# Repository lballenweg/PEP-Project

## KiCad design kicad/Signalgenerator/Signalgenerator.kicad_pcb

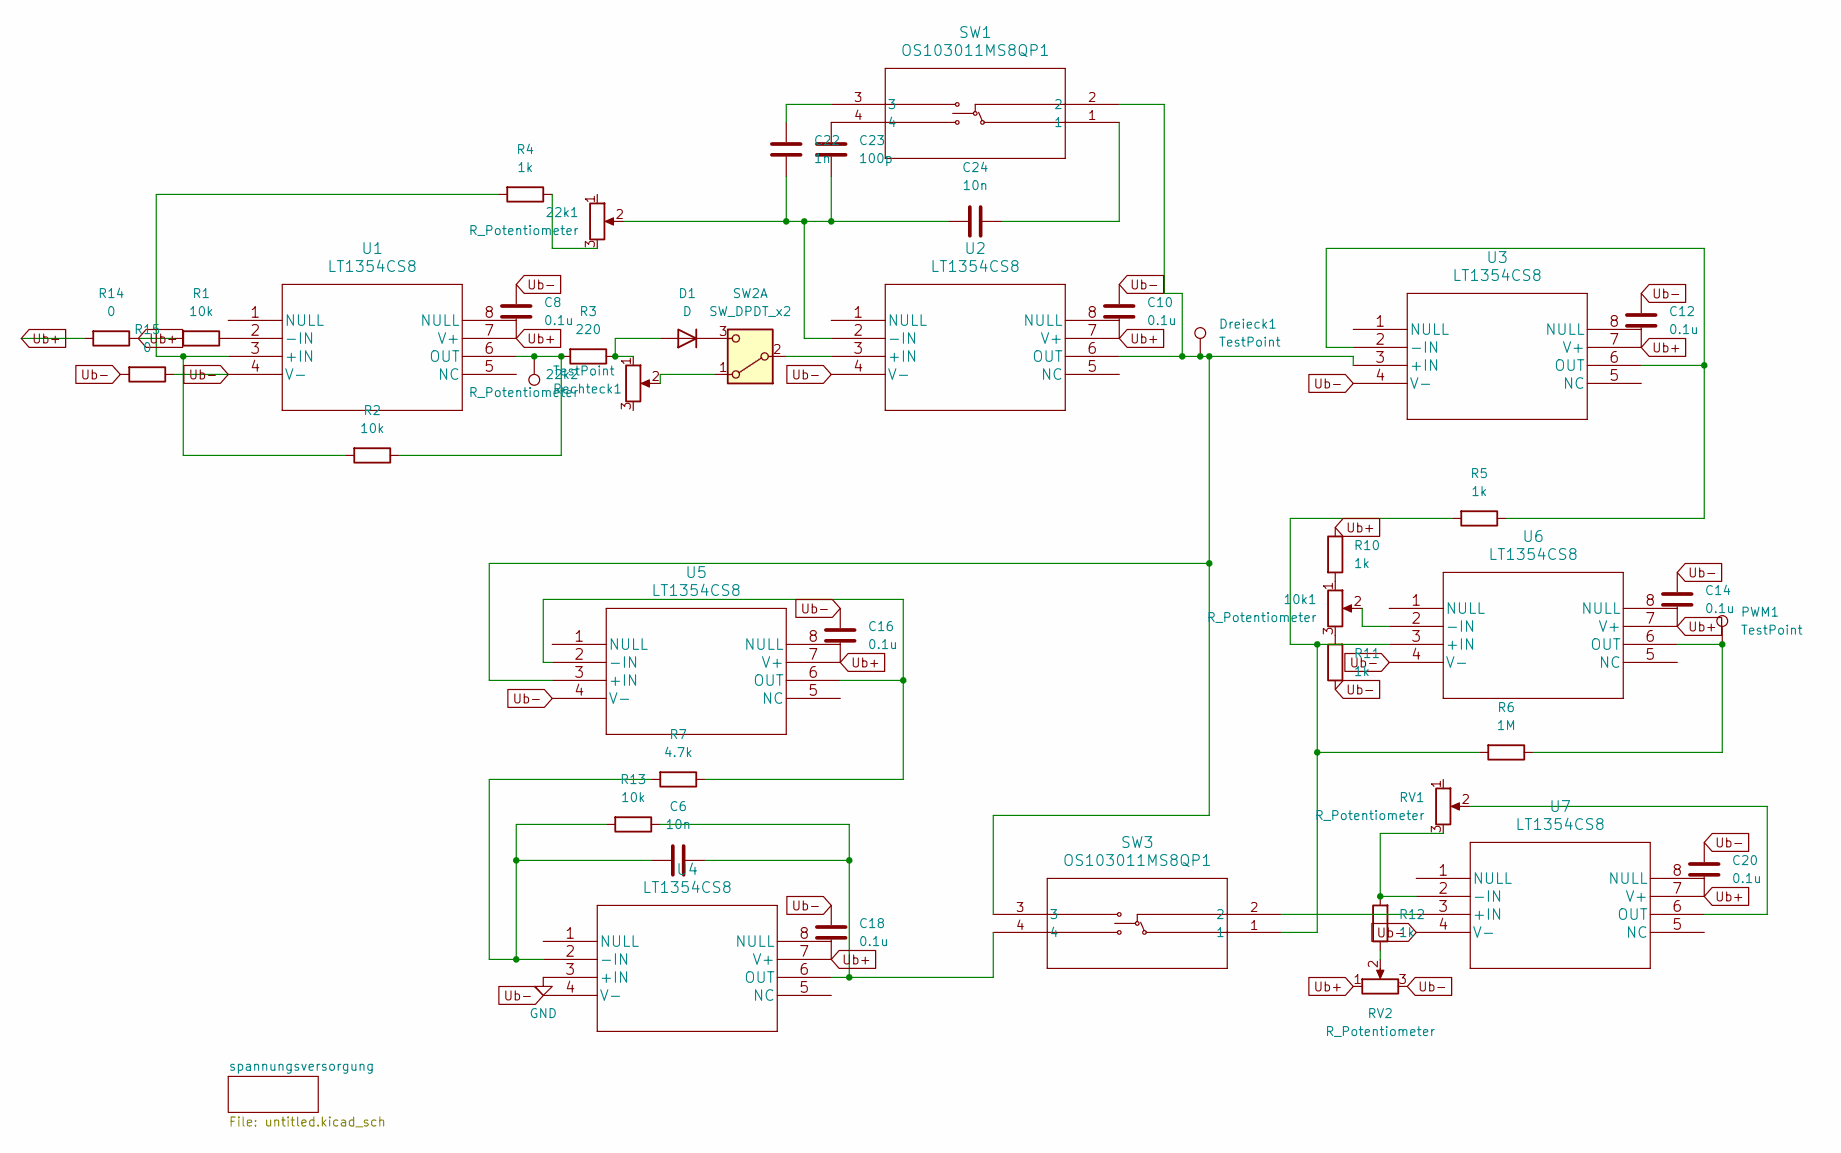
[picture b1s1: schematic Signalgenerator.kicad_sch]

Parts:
10k1, 22k1, 22k2: R_Potentiometer; Potentiometer_Vishay_T7-YA_Single_Vertical
C6, C24: 10n; C_0603_1608Metric_Pad1.08x0.95mm_HandSolder
C8, C10, C12, C14, C16, C18, C20: 0.1u; C_0603_1608Metric_Pad1.08x0.95mm_HandSolder
C22: 1n; C_0603_1608Metric_Pad1.08x0.95mm_HandSolder
C23: 100p; C_0603_1608Metric_Pad1.08x0.95mm_HandSolder
D1: D; D_A-405_P2.54mm_Vertical_AnodeUp
Dreieck1: TestPoint; TestPoint_Pad_D1.0mm
PWM1: TestPoint; TestPoint_Pad_D1.0mm
R1, R2, R13: 10k; R_0805_2012Metric_Pad1.20x1.40mm_HandSolder
R3: 220; R_0805_2012Metric_Pad1.20x1.40mm_HandSolder
R4, R5, R10, R11, R12: 1k; R_0805_2012Metric_Pad1.20x1.40mm_HandSolder
R6: 1M; R_0805_2012Metric_Pad1.20x1.40mm_HandSolder
R7: 4.7k; R_0805_2012Metric_Pad1.20x1.40mm_HandSolder
R14, R15: 0; R_0805_2012Metric_Pad1.20x1.40mm_HandSolder
RV1, RV2: R_Potentiometer; Potentiometer_Vishay_T7-YA_Single_Vertical
Rechteck1: TestPoint; TestPoint_Pad_D1.0mm
SW1, SW3: OS103011MS8QP1
SW2: SW_DPDT_x2; SW_Slide_SPDT_Straight_CK_OS102011MS2Q
U1, U2, U3, U4, U5, U6, U7: LT1354CS8; LT1354CS8-PBF

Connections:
GND: U4.3 (+IN); also elsewhere on the board
unnamed: 10k1.1, R10.2
unnamed: 10k1.3, R11.2
unnamed: 22k1.3, R4.1
unnamed: C22.2, SW1.3
unnamed: C23.2, SW1.4
unnamed: C24.1, SW1.1
unnamed: 22k2.1, D1.2 (A), R3.1
unnamed: D1.1 (K), SW2.3 (C)
unnamed: R12.1, RV2.2
unnamed: 22k2.2, SW2.1 (A)
unnamed: SW2.2 (B), U2.3 (+IN)
unnamed: R2.2, R4.2, U1.3 (+IN)
unnamed: R1.1, U1.2 (-IN)
unnamed: R2.1, R3.2, Rechteck1.1, U1.6 (OUT)
unnamed: 22k1.2, C22.1, C23.1, C24.2, U2.2 (-IN)
unnamed: Dreieck1.1, SW1.2, SW3.3, U2.6 (OUT), U3.3 (+IN), U5.3 (+IN)
unnamed: R5.1, U3.2 (-IN), U3.6 (OUT)
unnamed: C6.2, R7.2, R13.2, U4.2 (-IN)
unnamed: C6.1, R13.1, SW3.4, U4.6 (OUT)
unnamed: R7.1, U5.2 (-IN), U5.6 (OUT)
unnamed: R5.2, R6.2, SW3.1, U6.3 (+IN)
unnamed: 10k1.2, U6.2 (-IN)
unnamed: PWM1.1, R6.1, U6.6 (OUT)
unnamed: SW3.2, U7.3 (+IN)
unnamed: R12.2, RV1.3, U7.2 (-IN)
unnamed: RV1.2, U7.6 (OUT)
Ub+: C8.2, C10.2, C12.2, C14.2, C16.2, C18.2, C20.2, R1.2, R10.1, R14.1, R14.2, RV2.1, U1.7 (V+), U2.7 (V+), U3.7 (V+), U4.7 (V+), U5.7 (V+), U6.7 (V+), U7.7 (V+); also elsewhere on the board
Ub-: C8.1, C10.1, C12.1, C14.1, C16.1, C18.1, C20.1, R11.1, R15.1, R15.2, RV2.3, U1.4 (V-), U2.4 (V-), U3.4 (V-), U4.4 (V-), U5.4 (V-), U6.4 (V-), U7.4 (V-); also elsewhere on the board

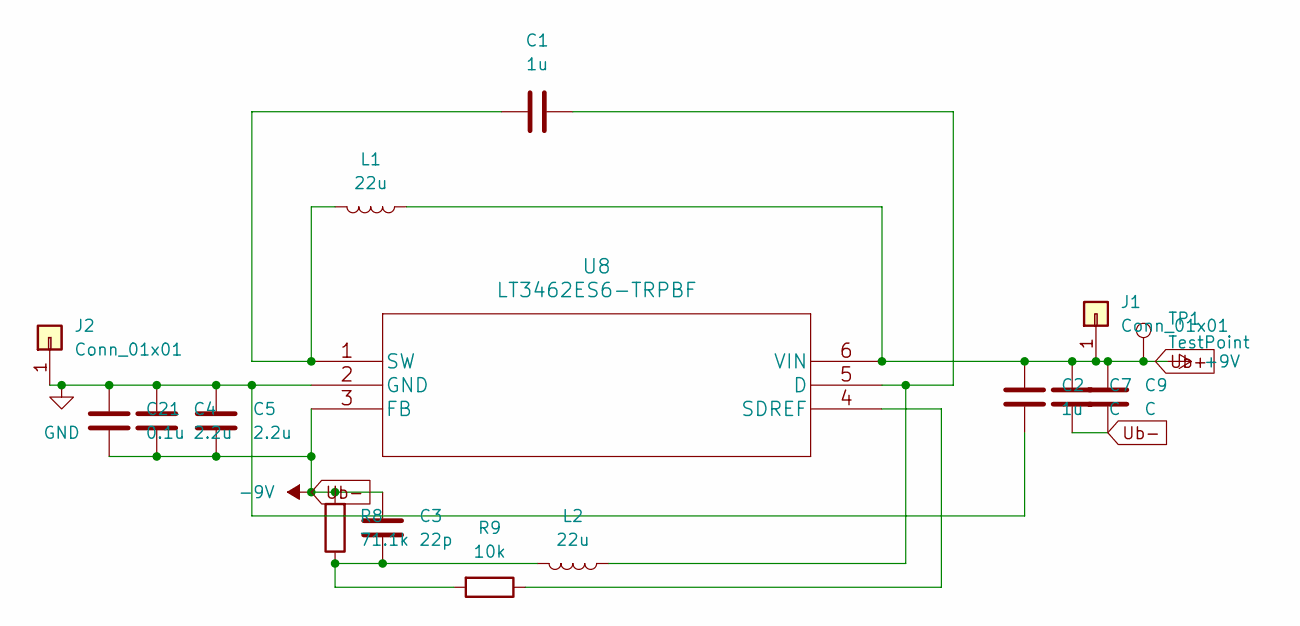
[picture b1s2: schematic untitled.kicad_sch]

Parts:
C1, C2: 1u; C_0603_1608Metric_Pad1.08x0.95mm_HandSolder
C3: 22p; C_0603_1608Metric_Pad1.08x0.95mm_HandSolder
C4, C5: 2.2u; C_0603_1608Metric_Pad1.08x0.95mm_HandSolder
C7, C9: C; C_0603_1608Metric_Pad1.08x0.95mm_HandSolder
C21: 0.1u; C_0603_1608Metric_Pad1.08x0.95mm_HandSolder
J1, J2: Conn_01x01; PinHeader_1x01_P2.54mm_Vertical
L1, L2: 22u; L_0603_1608Metric_Pad1.05x0.95mm_HandSolder
R8: 71.1k; R_0805_2012Metric_Pad1.20x1.40mm_HandSolder
R9: 10k; R_0805_2012Metric_Pad1.20x1.40mm_HandSolder
TP1: TestPoint; TestPoint_THTPad_2.0x2.0mm_Drill1.0mm
U8: LT3462ES6-TRPBF

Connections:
GND: C2.1, C4.2, C5.2, C21.1, J2.1, U8.2 (GND); also elsewhere on the board
unnamed: C3.1, L2.2, R8.1, R9.2
unnamed: C1.1, L2.1, U8.5 (D)
unnamed: R9.1, U8.4 (SDREF)
unnamed: C1.2, L1.2, U8.1 (SW)
Ub+: C2.2, C7.1, C9.1, J1.1, L1.1, TP1.1, U8.6 (VIN); also elsewhere on the board
Ub-: C3.2, C4.1, C5.1, C7.2, C9.2, C21.2, R8.2, U8.3 (FB); also elsewhere on the board

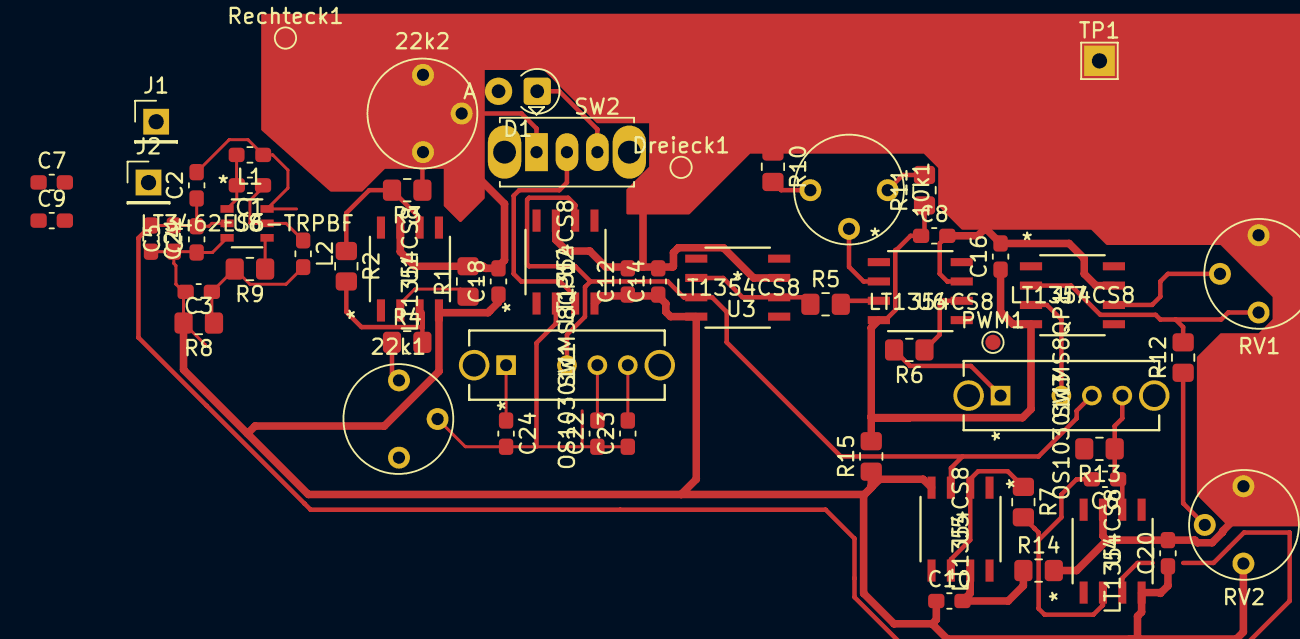
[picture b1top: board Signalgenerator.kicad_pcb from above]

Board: 2 copper layers, 59 parts (0 on the bottom side), 33 nets.

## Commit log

2026-05-14 neue Spannungsversorgung
2026-05-18 KiCad shaltplan
2026-05-19 Platine layout angefangen. Probleme mit Überkreuzungen.
2026-05-21 simulation angepasst
2026-05-21 Kondensatoren angepasst
2026-05-24 kleine änderungen
2026-05-24 layout zwischenstand
2026-05-25 rechteck dreieck hässlich
2026-05-25 aktueller stand
2026-05-25 schaltplan angepasst
2026-05-25 stand jetzt
2026-05-25 changed changes
2026-05-25 did things
2026-05-25 done da ting
2026-05-25 U du da rest

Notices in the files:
parts and their libraries:
Copyright 2016 Accelerated Designs. All rights reserved.
